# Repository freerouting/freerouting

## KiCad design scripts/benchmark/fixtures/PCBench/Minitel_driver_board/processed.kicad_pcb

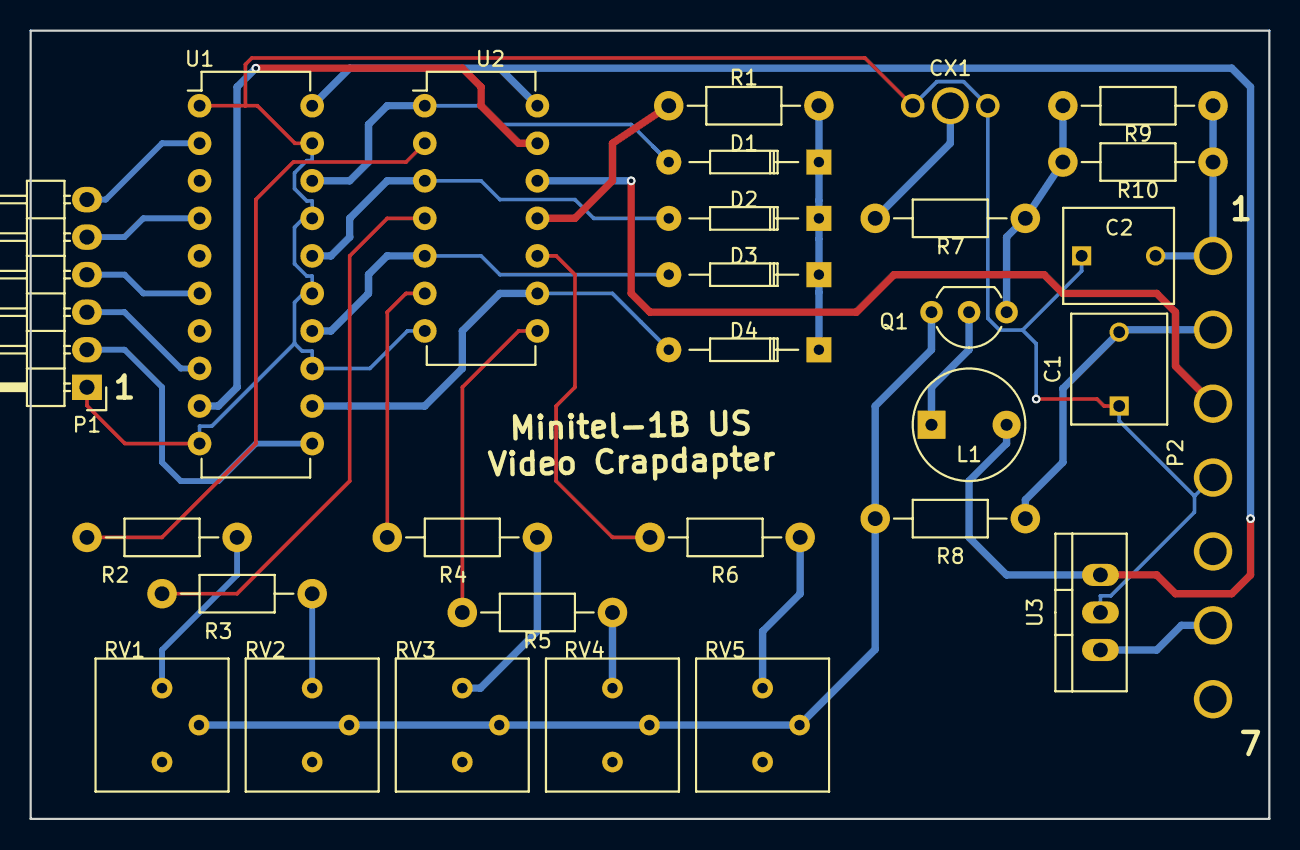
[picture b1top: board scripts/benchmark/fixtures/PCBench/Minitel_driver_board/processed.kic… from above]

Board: 2 copper layers, 83.8 x 53.3 mm, 29 parts (0 on the bottom side), 32 nets.

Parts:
C1: 10nF; C_Rect_L7.5_W6.5_P5
C2: 100nF; C_Rect_L7.5_W6.5_P5
CX1: COAX; COAX-SHLD
D1, D2, D3, D4: 1N4148; Diode_DO-35_SOD27_Horizontal_RM10
L1: 20uH; INDUCTOR_V
P1: CONN_01X06; Pin_Header_Angled_1x06
P2: CONN_01X07; CONN-1x7-5mm-pitch
Q1: C5468; TO-92_Inline_Wide
R1: 680; Resistor_Horizontal_RM10mm
R2: 4K; Resistor_Horizontal_RM10mm
R3: 1.8K; Resistor_Horizontal_RM10mm
R4: 1K; Resistor_Horizontal_RM10mm
R5: 460; Resistor_Horizontal_RM10mm
R6: 620; Resistor_Horizontal_RM10mm
R7: 100; Resistor_Horizontal_RM10mm
R8: 1.2K; Resistor_Horizontal_RM10mm
R9, R10: 2.4K; Resistor_Horizontal_RM10mm
RV1, RV2, RV3, RV4, RV5: POT; Potentiometer_Cermet_CT-6EP
U1: 74LS244; DIP-20_W7.62mm
U2: 74HC04; DIP-14_W7.62mm
U3: 7805; TO-220_Neutral123_Vertical

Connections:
GND: C1.1, C2.1, CX1.2, CX1.3, P1.1, P2.4, U1.1, U1.10, U1.13, U1.15, U1.17, U1.19, U2.7, U3.2
unnamed: C1.2, P2.2, R8.1
unnamed: C2.2, P2.1, R9.1, R10.1
unnamed: CX1.1, R7.1
unnamed: D1.1, D2.1, D3.1, D4.1, R1.2
unnamed: D1.2, U1.18, U2.1
unnamed: D2.2, U1.16, U2.3
unnamed: D3.2, U1.14, U2.5
unnamed: D4.2, U1.12, U2.9
unnamed: L1.1, Q1.2
unnamed: P1.2, U1.11
unnamed: P1.3, U1.8
unnamed: P1.4, U1.6
unnamed: P1.5, U1.4
unnamed: P1.6, U1.2
unnamed: P2.3, U2.12
unnamed: P2.6, U3.1
unnamed: Q1.1, R7.2, R9.2, R10.2
unnamed: Q1.3, R8.2, RV1.2, RV2.2, RV3.2, RV4.2, RV5.2
unnamed: R1.1, U2.11
unnamed: R2.1, RV1.1
unnamed: R2.2, U2.2
unnamed: R3.1, RV2.1
unnamed: R3.2, U2.4
unnamed: R4.1, RV3.1
unnamed: R4.2, U2.6
unnamed: R5.1, RV4.1
unnamed: R5.2, U2.8
unnamed: R6.1, RV5.1
unnamed: R6.2, U2.10
SYNC: U1.9, U2.13
VCC: L1.2, U1.20, U2.14, U3.3

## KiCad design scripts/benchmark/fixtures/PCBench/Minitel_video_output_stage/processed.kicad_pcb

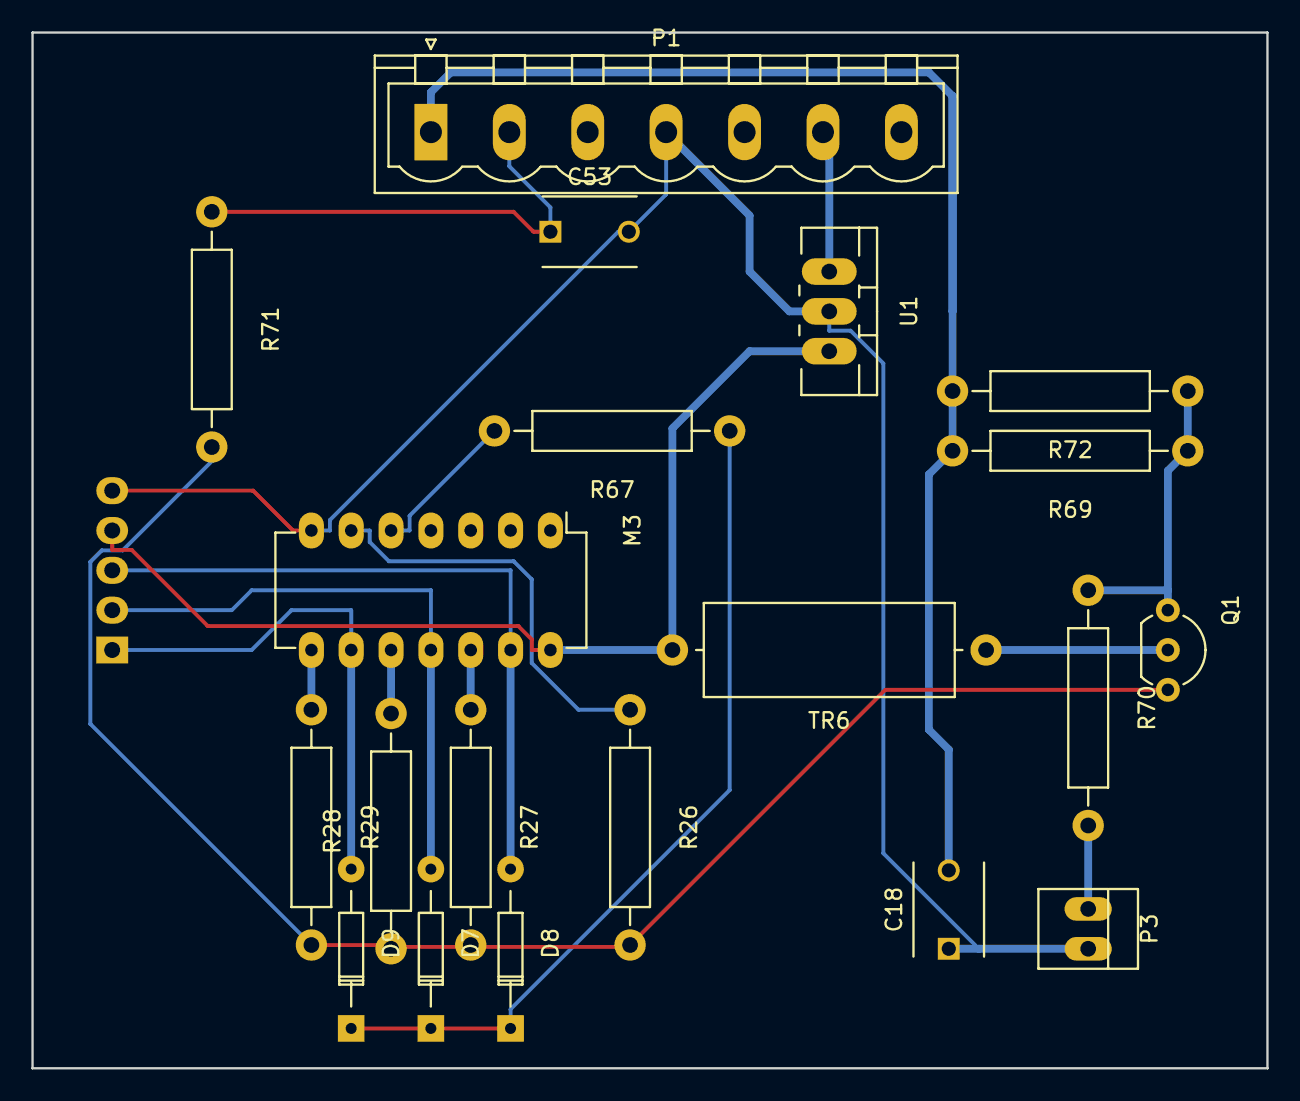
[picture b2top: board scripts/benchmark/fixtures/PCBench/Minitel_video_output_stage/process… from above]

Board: 2 copper layers, 78.7 x 66.0 mm, 21 parts (1 on the bottom side), 18 nets.

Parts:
C18: 100nF; C_Disc_D6_P5
C53: 10nF; C_Disc_D6_P5
D7, D8, D9: 1N4148; Diode_DO-35_SOD27_Horizontal_RM10
M3: 74HC04; DIP-14_W7.62mm_LongPads
P1: CONN_01X07; PhoenixContact_MSTBVA-G_07x5.00mm_Vertical
P2: CONN_01X05; Pin_Header_Straight_1x05
P3: BNC; PINHEAD1-2
Q1: C5468; TO-92_Inline_Wide
R26: 620; Resistor_Horizontal_RM15mm
R27: 1.8K; Resistor_Horizontal_RM15mm
R28: 460; Resistor_Horizontal_RM15mm
R29: 1K; Resistor_Horizontal_RM15mm
R67: 670; Resistor_Horizontal_RM15mm
R69, R72: 2.4K; Resistor_Horizontal_RM15mm
R70: 100; Resistor_Horizontal_RM15mm
R71: 1.2K; Resistor_Horizontal_RM15mm
TR6: 20uH; Choke_Horizontal_RM20mm
U1: 7805; TO-220_Neutral123_Vertical_LargePads

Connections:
+5V: M3.14, P2.4, TR6.2, U1.3
CH_BLUE: D9.2, M3.9, P2.1
CH_GREEN: D7.2, M3.11, P2.2
CH_RED: D8.2, M3.13, P2.3
GND: C18.1, C53.2, M3.7, P1.4, P2.5, P3.2, U1.2
unnamed: C18.2, P1.1, R69.2, R72.2
unnamed: C53.1, P1.2, R71.1
unnamed: D7.1, D8.1, D9.1, R67.1
unnamed: M3.5, R67.2
unnamed: M3.6, R26.1
unnamed: M3.8, R29.1
unnamed: M3.10, R28.2
unnamed: M3.12, R27.1
unnamed: Q1.1, R69.1, R70.1, R72.1
unnamed: Q1.2, TR6.1
unnamed: Q1.3, R26.2, R27.2, R28.1, R29.2, R71.2
VIDEO_OUT: P3.1, R70.2
VIN: P1.6, U1.1

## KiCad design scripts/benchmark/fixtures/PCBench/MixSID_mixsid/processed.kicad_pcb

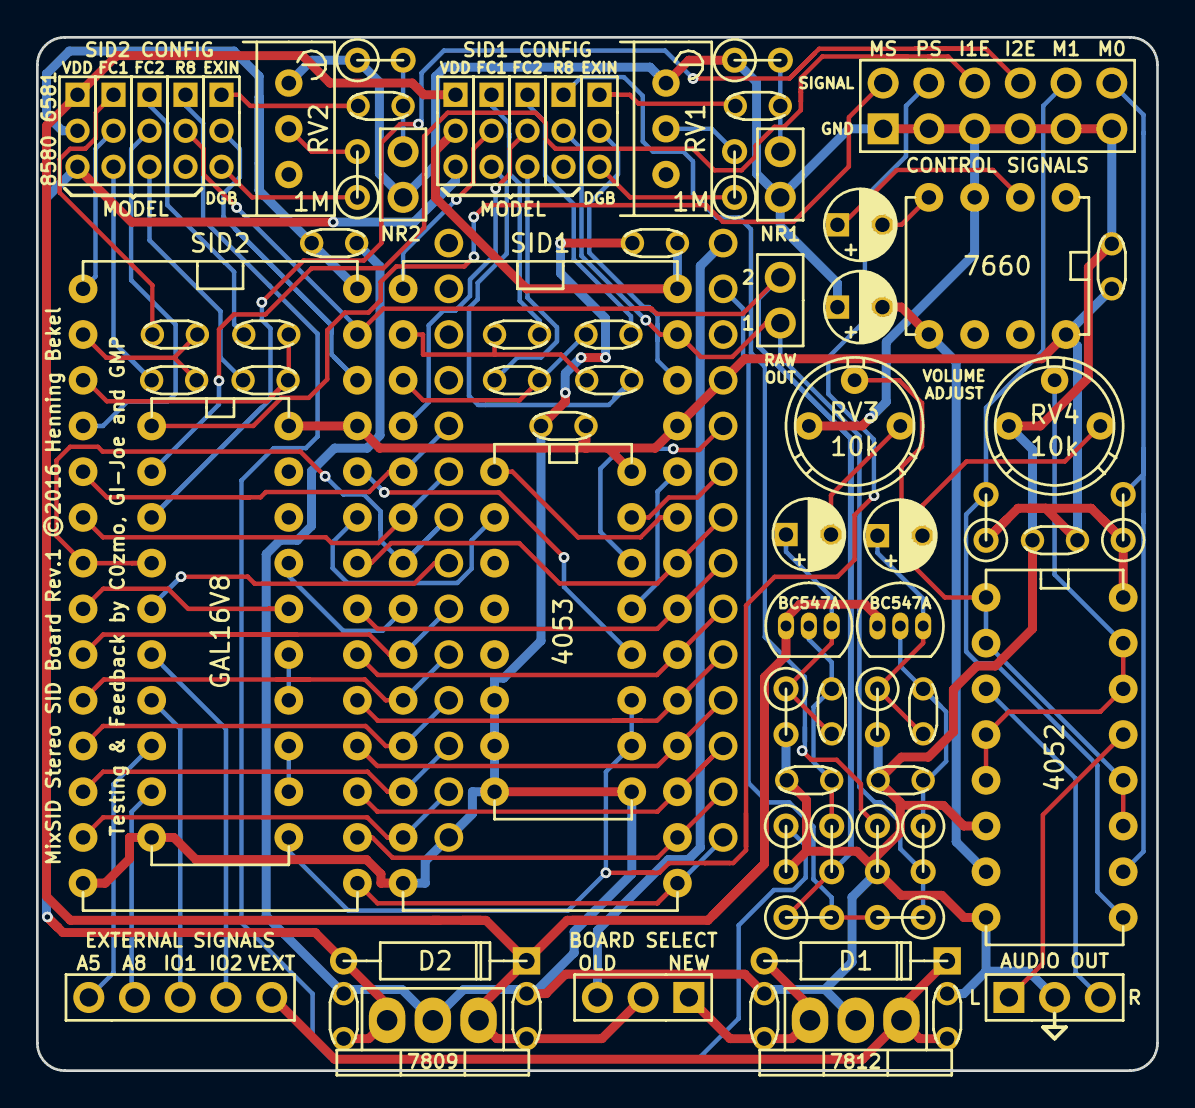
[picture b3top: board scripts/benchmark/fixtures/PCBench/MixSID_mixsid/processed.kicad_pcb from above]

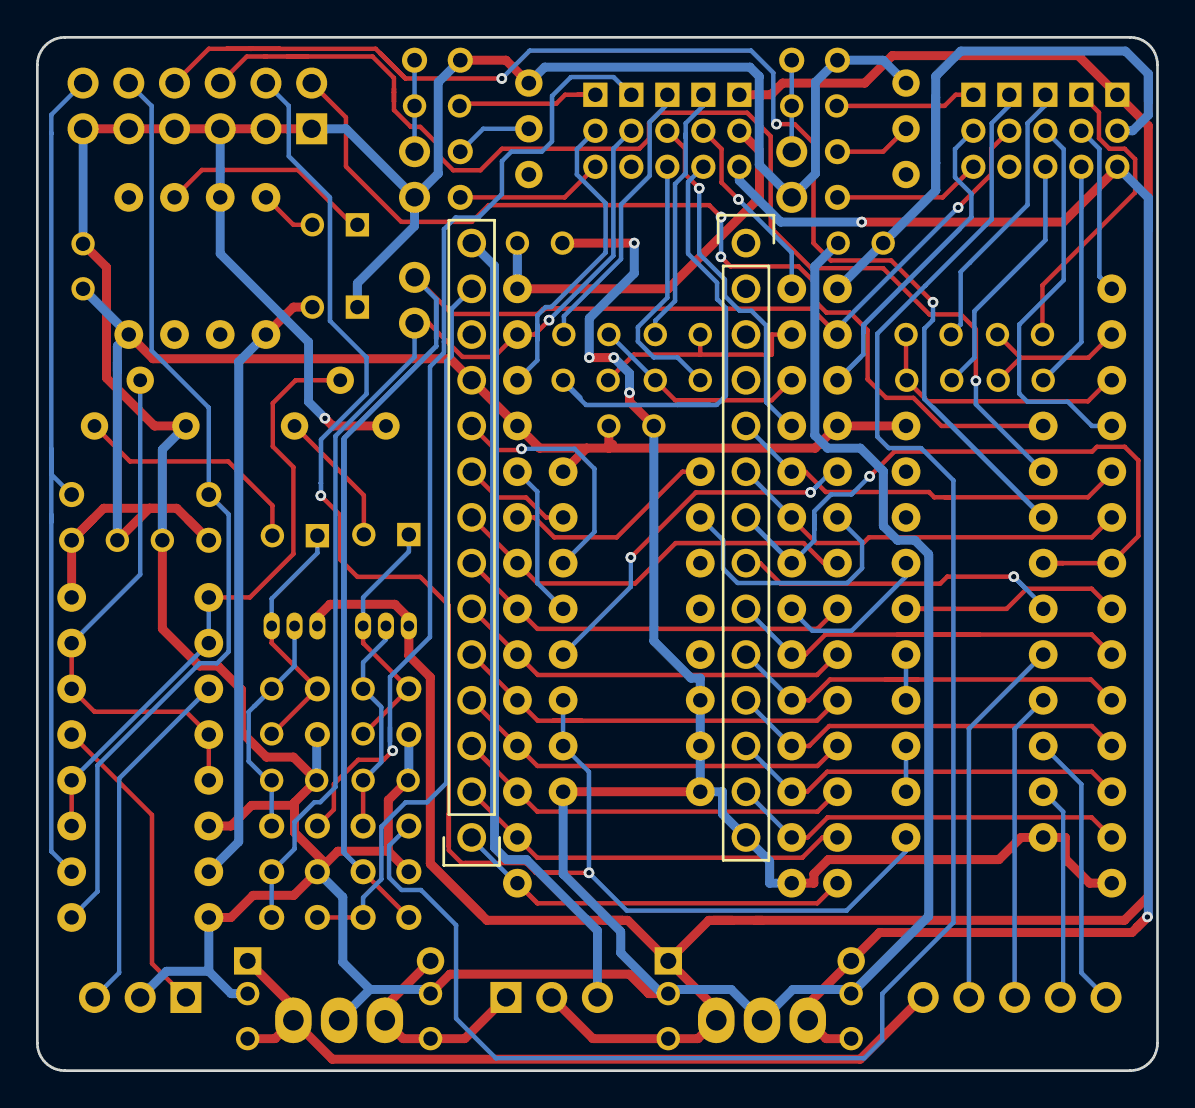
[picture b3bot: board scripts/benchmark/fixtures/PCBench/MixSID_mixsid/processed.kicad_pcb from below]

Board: 2 copper layers, 62.2 x 57.4 mm, 76 parts (2 on the bottom side), 90 nets.

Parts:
C1, C3, C5, C7, C9, C11, C16, C21: 470p; C_Disc_D3_P2.5
C2, C4, C10, C12: 22n; C_Disc_D3_P2.5
C6, C8, C13, C14, C23, C24, C25, C26, C27: 100n; C_Disc_D3_P2.5
C15, C20: 1n; C_Disc_D3_P2.5
C17, C18: 10u; C_Radial_D5_L6_P2.5
C19, C22: 10uF; C_Radial_D5_L6_P2.5
D1, D2: 1N4002; DO-41
JP1: SUPPLY2; Pin_Header_Straight_1x03_Pitch2.00mm_Jumper_1-2
JP2: S2CAP2; Pin_Header_Straight_1x03_Pitch2.00mm_Jumper_1-2
JP3: S2CAP1; Pin_Header_Straight_1x03_Pitch2.00mm
JP4: BOARD; Pin_Header_Straight_1x03
JP5: SUPPLY1; Pin_Header_Straight_1x03_Pitch2.00mm_Jumper_2-3
JP6: S1CAP2; Pin_Header_Straight_1x03_Pitch2.00mm_Jumper_2-3
JP7: S1CAP1; Pin_Header_Straight_1x03_Pitch2.00mm_Jumper_2-3
JP8: INPUT2; Pin_Header_Straight_1x03_Pitch2.00mm_Jumper_1-2
JP9: NR1; Pin_Header_Straight_1x02
JP10: NR2; Pin_Header_Straight_1x02
JP11: INPUT1; Pin_Header_Straight_1x03_Pitch2.00mm_Jumper_2-3
JP12: J2R8; Pin_Header_Straight_1x03_Pitch2.00mm_Jumper_1-2
JP13: J1R8; Pin_Header_Straight_1x03_Pitch2.00mm_Jumper_2-3
P1: INPUT; Pin_Header_Straight_1x05
P2: CONTROL; Pin_Header_Straight_2x06
P3: RAW; Pin_Header_Straight_1x02
P4: SOCKET LEFT; Pin_Header_Straight_1x14
P5: OUTPUT; Pin_Header_Straight_1x03
P6: SOCKET RIGHT; Pin_Header_Straight_1x14
Q1, Q2: BC547; TO-92_Inline_Narrow_Oval
R1, R10: 220k; R1
R2, R9: 100k; R1
R3, R5, R6, R12, R13, R14: 1k; R1
R4, R11: 10k; R1
R7, R8: 4k7; R1
RV1, RV2: 1M; Potentiometer_Bourns_3296W_3-8Zoll_Inline_ScrewUp
RV3, RV4: 10k; Potentiometer_Bourns_3339P_Angular_ScrewUp
U1: GAL16V8; DIP-20_W7.62mm
U2: SID2; DIP-28_W15.24mm
U3: 7812; TO-220
U4: 7809; TO-220
U5: SID1; DIP-28_W15.24mm
U6: 4052; DIP-16_W7.62mm
U7: 4053; DIP-16_W7.62mm
U8: 7660; DIP-8_W7.62mm

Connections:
/+9V: C8.1, D2.2, JP1.3, JP5.3, U4.3
/+12V: C7.1, D2.1, JP1.1, JP4.2, JP5.1, Q1.1, Q2.1, U4.1
/A0: P4.9, U2.9, U5.9
/A1: P4.10, U2.10, U5.10
/A2: P4.11, U2.11, U5.11
/A3: P4.12, U2.12, U5.12
/A4: P4.13, U2.13, U5.13
/A5: P1.1, U1.8
/A8: P1.2, U1.9
/CLK: P4.6, U2.6, U5.6
/D0: P6.1, U2.15, U5.15
/D1: P6.2, U2.16, U5.16
/D2: P6.3, U2.17, U5.17
/D3: P6.4, U2.18, U5.18
/D4: P6.5, U2.19, U5.19
/D5: P6.6, U2.20, U5.20
/D6: P6.7, U2.21, U5.21
/D7: P6.8, U2.22, U5.22
/LEFT: RV3.2, U6.1, U6.2, U6.11, U6.12
/LEFT_OUT: P5.1, U6.13
/M0: P2.12, R7.2, U6.10
/M1: P2.10, R8.2, U6.9
/MONO_OUT: P6.13, R13.2, R14.2
/MS: P2.2, U1.1
/POTX: P6.10, U7.14
/POTX1: U5.24, U7.13
/POTX2: U2.24, U7.12
/POTY: P6.9, U7.15
/POTY1: U5.23, U7.1
/POTY2: U2.23, U7.2
/PS: P2.4, U1.11, U7.10, U7.11
/PWR: C6.1, D1.2, JP4.1, U3.3
/PWR1: C27.1, JP5.2, U5.28
/PWR2: C26.1, JP1.2, U2.28
/RIGHT: RV4.2, U6.4, U6.5, U6.14, U6.15
/RIGHT_OUT: P5.3, U6.3
/RW: P4.7, U1.4, U2.7, U5.7
/S1IN: JP11.2, U5.26
/S1OUT: JP13.2, P3.2, R11.2, R14.1, U5.27
/S2IN: JP8.2, U2.26
/S2OUT: JP12.2, P3.1, R4.2, R13.1, U2.27
/VEE: C18.2, U6.7, U8.5
/VEXT: C5.1, D1.1, P1.5, U3.1
/~CS: P4.8, U1.5
/~CS1: U1.17, U5.8
/~CS2: U1.16, U2.8
/~IO1: P1.3, U1.7
/~IO1EN: P2.6, U1.2
/~IO2: P1.4, U1.6
/~IO2EN: P2.8, U1.3
/~RES: P4.5, U2.5, U5.5
GND: C5.2, C6.2, C7.2, C8.2, C15.2, C18.1, C20.2, C23.2, C24.2, C25.2, C26.2, C27.2, JP9.2, JP10.2, P2.1, P2.3, P2.5, P2.7, P2.9, P2.11, P4.14, P5.2, R2.1, R3.2, R5.2, R6.2, R9.1, R12.2, RV1.1, RV2.1, RV3.1, RV4.1, U1.10, U2.14, U3.2, U4.2, U5.14, U6.6, U6.8, U7.6, U7.7, U7.8, U7.9, U8.3
unnamed: C1.1, C2.2, U2.3
unnamed: C1.2, JP2.1
unnamed: C2.1, JP2.3
unnamed: C3.1, C4.2, U2.2
unnamed: C3.2, JP3.1
unnamed: C4.1, JP3.3
unnamed: C9.2, JP6.1
unnamed: C10.1, JP6.3
unnamed: C9.1, C10.2, U5.3
unnamed: C11.1, C12.2, U5.2
unnamed: C11.2, JP7.1
unnamed: C12.1, JP7.3
unnamed: C13.1, JP10.1, R9.2
unnamed: C13.2, JP8.1
unnamed: C14.1, JP9.1, R2.2
unnamed: C14.2, JP11.1
unnamed: C15.1, C16.1, Q1.2, R4.1
unnamed: C16.2, C19.1, Q1.3, R5.1
unnamed: C17.1, U8.2
unnamed: C17.2, U8.4
unnamed: C19.2, RV3.3
unnamed: C20.1, C21.1, Q2.2, R11.1
unnamed: C21.2, C22.1, Q2.3, R12.1
unnamed: C22.2, RV4.3
unnamed: JP2.2, U2.4
unnamed: JP3.2, U2.1
unnamed: JP6.2, U5.4
unnamed: JP7.2, U5.1
unnamed: JP8.3, R1.1
unnamed: JP11.3, R10.1
unnamed: JP12.1, R3.1
unnamed: JP13.1, R6.1
unnamed: R1.2, RV2.2
unnamed: R10.2, RV1.2
unnamed: U1.12, U1.13
unnamed: U1.14, U1.15
VCC: C23.1, C24.1, C25.1, P6.11, R7.1, R8.1, U1.20, U2.25, U5.25, U6.16, U7.16, U8.8
VDD: JP4.3, P6.14

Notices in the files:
scripts/benchmark/fixtures/PCBench/MixSID_mixsid/processed.kicad_pcb:
MixSID Stereo SID Board Rev.1 ©2016 Henning Bekel
